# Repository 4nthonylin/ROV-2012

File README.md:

ROV-2012
========

Schematics, Code

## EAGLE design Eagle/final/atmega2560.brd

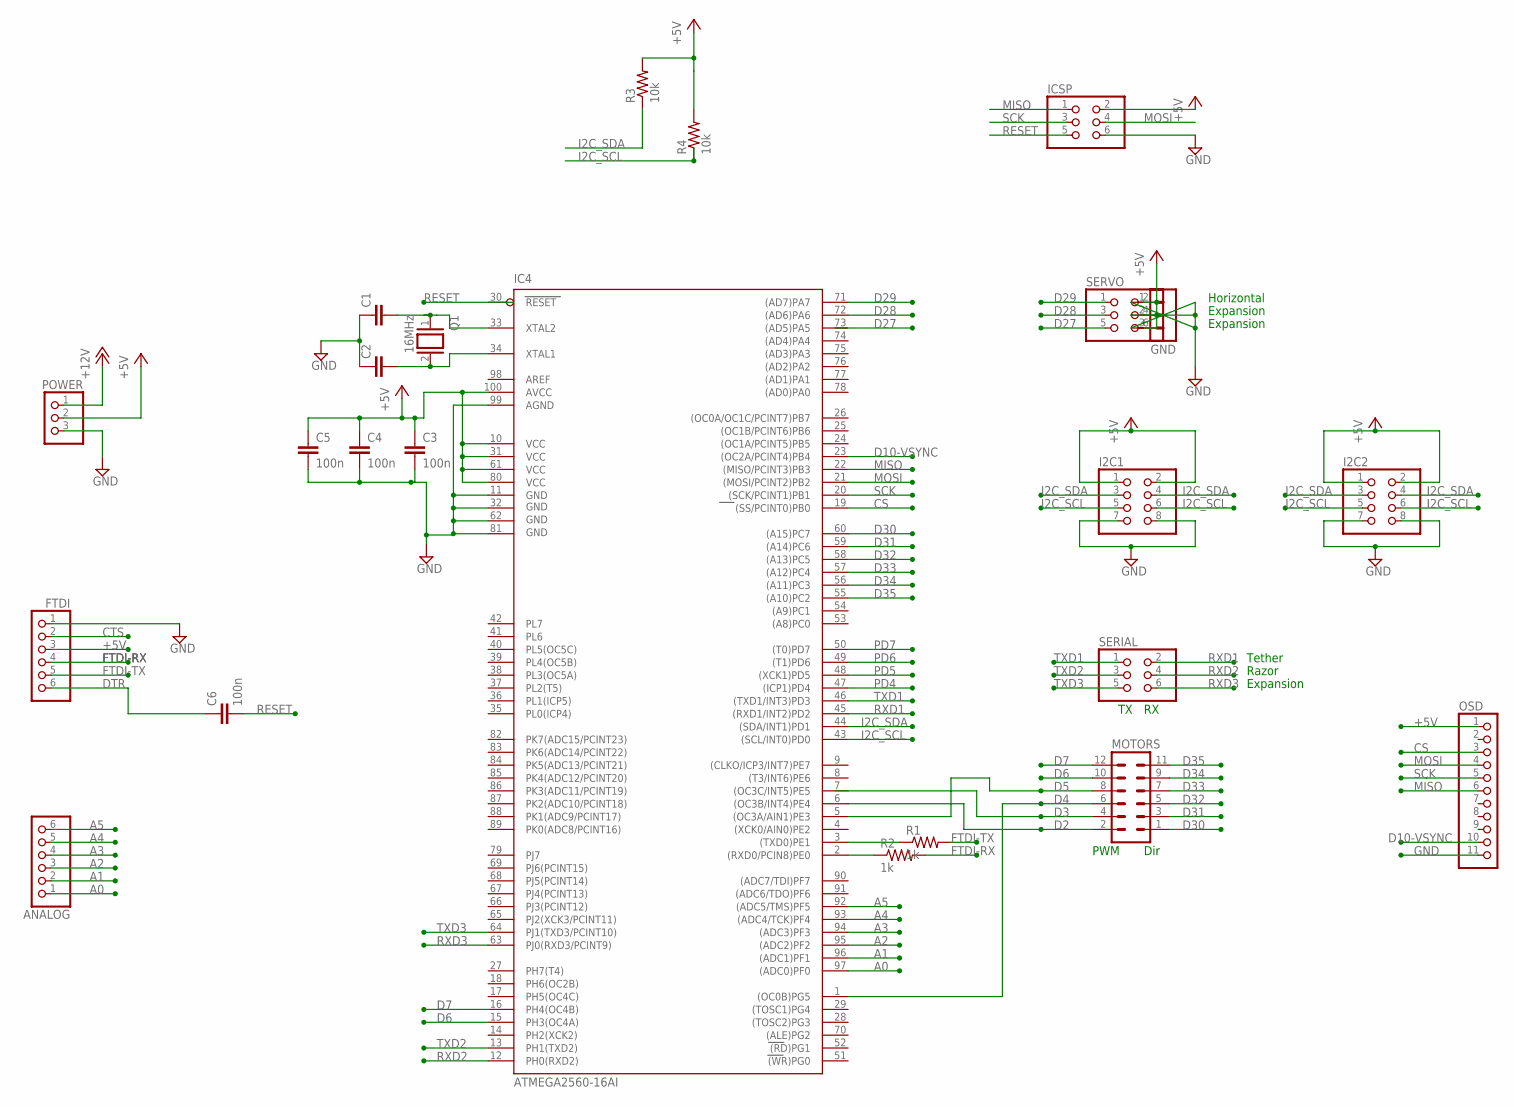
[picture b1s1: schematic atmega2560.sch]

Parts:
ANALOG: PINHD-1X6; 1X06
C1, C2: C5/3.5; C5B3.5
C3, C4, C5: 100n; C5B3.5
C6: 100n; C050-030X075
FTDI: PINHD-1X6; 1X06
GND: MA03-1
I2C1, I2C2: PINHD-2X4; 2X04
IC4: ATMEGA2560-16AI; TQFP100
ICSP: PINHD-2X3; 2X03
MOTORS: MA06-2
OSD: PINHD-1X11; 1X11
POWER: PINHD-1X3; 1X03
Q1: 16MHz; QS
R1, R2: 1k; 0207/7
R3, R4: 10k; 0207/7
SERIAL: PINHD-2X3; 2X03
SERVO: PINHD-2X3; 2X03

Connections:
+5V: C3.1, C4.1, C5.1, FTDI.3, I2C1.1, I2C1.2, I2C2.1, I2C2.2, IC4.10 (VCC), IC4.31 (VCC1), IC4.61 (VCC2), IC4.80 (VCC3), IC4.100 (AVCC), ICSP.2, OSD.1, POWER.2, R3.2, R4.2, SERVO.2, SERVO.4, SERVO.6
+12V: POWER.1
A0: ANALOG.1, IC4.97 ((ADC0)PF0)
A1: ANALOG.2, IC4.96 ((ADC1)PF1)
A2: ANALOG.3, IC4.95 ((ADC2)PF2)
A3: ANALOG.4, IC4.94 ((ADC3)PF3)
A4: ANALOG.5, IC4.93 ((ADC4/TCK)PF4)
A5: ANALOG.6, IC4.92 ((ADC5/TMS)PF5)
CS: IC4.19 ((SS/PCINT0)PB0), OSD.3
CTS: FTDI.2
D2: IC4.6 ((OC3B/INT4)PE4), MOTORS.2
D3: MOTORS.4
D4: IC4.1 ((OC0B)PG5), MOTORS.6
D5: IC4.5 ((OC3A/AIN1)PE3), MOTORS.8
D6: IC4.15 (PH3(OC4A)), MOTORS.10
D7: IC4.16 (PH4(OC4B)), MOTORS.12
D10-VSYNC: IC4.23 ((OC2A/PCINT4)PB4), OSD.10
D27: SERVO.5
D28: IC4.72 ((AD6)PA6), SERVO.3
D29: IC4.71 ((AD7)PA7), SERVO.1
D30: IC4.60 ((A15)PC7), MOTORS.1
D31: IC4.59 ((A14)PC6), MOTORS.3
D32: IC4.58 ((A13)PC5), MOTORS.5
D33: IC4.57 ((A12)PC4), MOTORS.7
D34: IC4.56 ((A11)PC3), MOTORS.9
D35: IC4.55 ((A10)PC2), MOTORS.11
DTR: C6.1, FTDI.6
FTDI-RX: FTDI.4, R2.2
FTDI-TX: FTDI.5, R1.2
GND: C1.1, C2.1, C3.2, C4.2, C5.2, FTDI.1, GND.1, GND.2, GND.3, I2C1.7, I2C1.8, I2C2.7, I2C2.8, IC4.11 (GND), IC4.32 (GND1), IC4.62 (GND2), IC4.81 (GND3), IC4.99 (AGND), ICSP.6, OSD.11, POWER.3
I2C_SCL: I2C1.5, I2C1.6, I2C2.5, I2C2.6, IC4.43 ((SCL/INT0)PD0), R4.1
I2C_SDA: I2C1.3, I2C1.4, I2C2.3, I2C2.4, IC4.44 ((SDA/INT1)PD1), R3.1
MISO: IC4.22 ((MISO/PCINT3)PB3), ICSP.1, OSD.6
MOSI: IC4.21 ((MOSI/PCINT2)PB2), ICSP.4, OSD.4
unnamed: C1.2, IC4.33 (XTAL2), Q1.1
unnamed: C2.2, IC4.34 (XTAL1), Q1.2
unnamed: IC4.2 ((RXD0/PCIN8)PE0), R2.1
unnamed: IC4.3 ((TXD0)PE1), R1.1
PD4: IC4.47 ((ICP1)PD4)
PD5: IC4.48 ((XCK1)PD5)
PD6: IC4.49 ((T1)PD6)
PD7: IC4.50 ((T0)PD7)
RESET: C6.2, ICSP.5
RXD1: IC4.45 ((RXD1/INT2)PD2), SERIAL.2
RXD2: IC4.12 (PH0(RXD2)), SERIAL.4
RXD3: IC4.63 (PJ0(RXD3/PCINT9)), SERIAL.6
SCK: IC4.20 ((SCK/PCINT1)PB1), ICSP.3, OSD.5
TXD1: IC4.46 ((TXD1/INT3)PD3), SERIAL.1
TXD2: IC4.13 (PH1(TXD2)), SERIAL.3
TXD3: IC4.64 (PJ1(TXD3/PCINT10)), SERIAL.5

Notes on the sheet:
PWM
Dir
Tether
Razor
Expansion
Horizontal

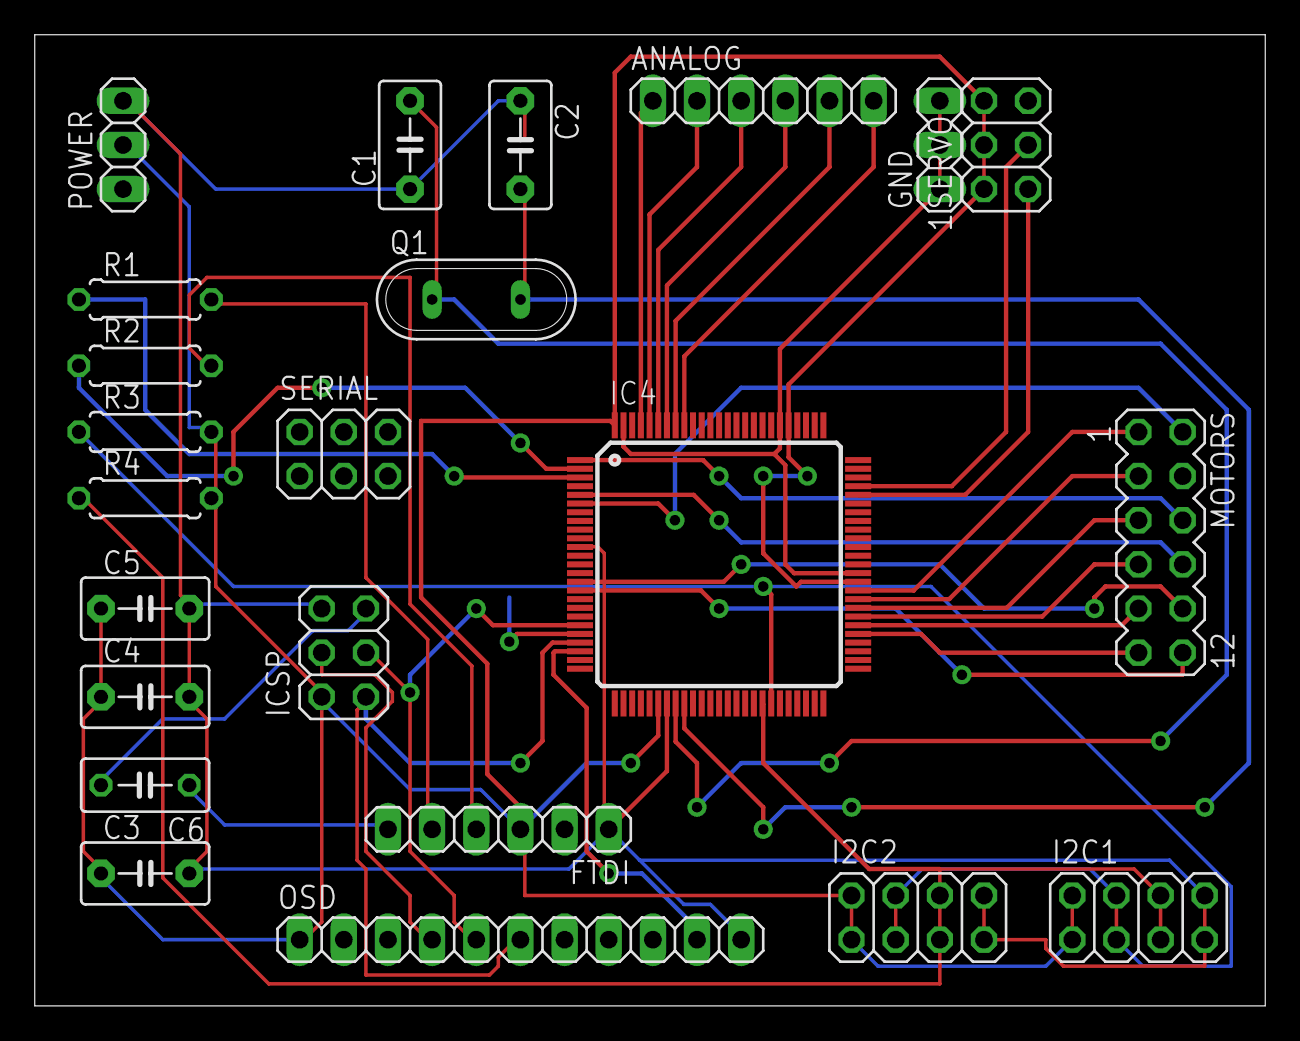
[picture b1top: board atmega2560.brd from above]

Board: 2 copper layers, 70.8 x 55.9 mm, 23 parts (0 on the bottom side), 42 nets.

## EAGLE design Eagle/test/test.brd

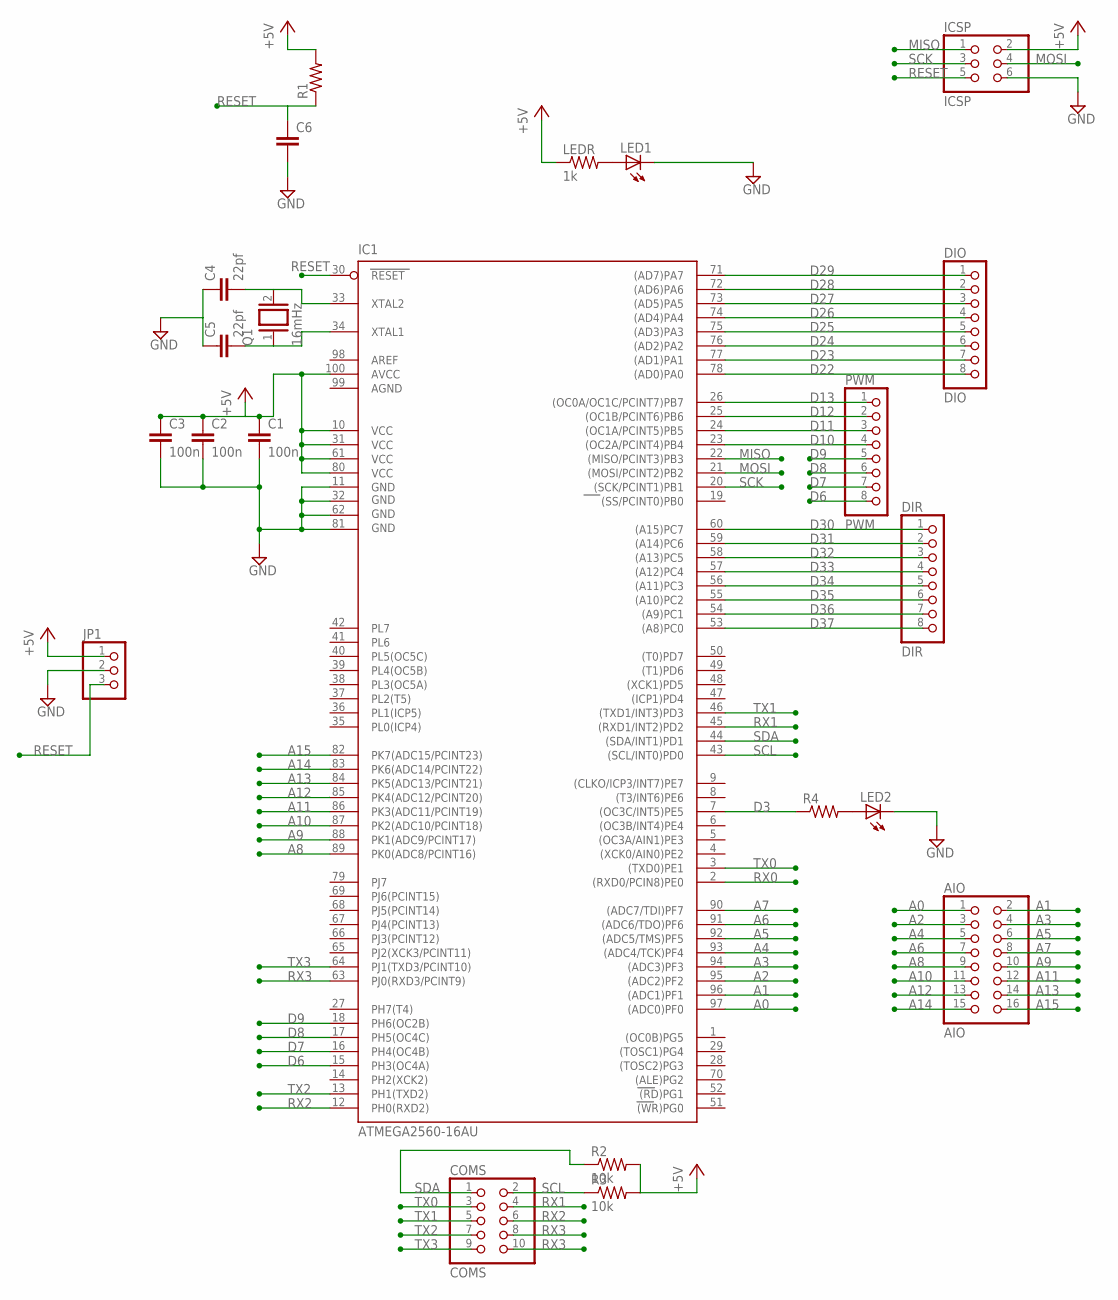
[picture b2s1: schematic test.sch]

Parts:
AIO: AIO; 2X08
C1, C2, C3: 100n; C5B3.5
C4, C5: 22pf; C5B3.5
C6: C5/3.5; C5B3.5
COMS: COMS; 2X05
DIO: DIO; 1X08
DIR: DIR; 1X08
IC1: ATMEGA2560-16AU; TQFP100
ICSP: ICSP; 2X03
JP1: PINHD-1X3; 1X03
LED1, LED2: LEDB156; Q62902-B156
LEDR: 1k; 0207/7
PWM: PWM; 1X08
Q1: 16mHz; QS
R1, R4: R-US_0207/7; 0207/7
R2, R3: 10k; 0207/7

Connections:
+5V: C1.1, C2.1, C3.1, IC1.10 (VCC), IC1.31 (VCC1), IC1.61 (VCC2), IC1.80 (VCC3), IC1.100 (AVCC), ICSP.2, JP1.1, LEDR.1, R1.2, R2.2, R3.2
A0: AIO.1, IC1.97 ((ADC0)PF0)
A1: AIO.2, IC1.96 ((ADC1)PF1)
A2: AIO.3, IC1.95 ((ADC2)PF2)
A3: AIO.4, IC1.94 ((ADC3)PF3)
A4: AIO.5, IC1.93 ((ADC4/TCK)PF4)
A5: AIO.6, IC1.92 ((ADC5/TMS)PF5)
A6: AIO.7, IC1.91 ((ADC6/TDO)PF6)
A7: AIO.8, IC1.90 ((ADC7/TDI)PF7)
A8: AIO.9, IC1.89 (PK0(ADC8/PCINT16))
A9: AIO.10, IC1.88 (PK1(ADC9/PCINT17))
A10: AIO.11, IC1.87 (PK2(ADC10/PCINT18))
A11: AIO.12, IC1.86 (PK3(ADC11/PCINT19))
A12: AIO.13, IC1.85 (PK4(ADC12/PCINT20))
A13: AIO.14, IC1.84 (PK5(ADC13/PCINT21))
A14: AIO.15, IC1.83 (PK6(ADC14/PCINT22))
A15: AIO.16, IC1.82 (PK7(ADC15/PCINT23))
AGND: IC1.99 (AGND)
D3: IC1.7 ((OC3C/INT5)PE5), R4.1
D6: IC1.15 (PH3(OC4A)), PWM.8
D7: IC1.16 (PH4(OC4B)), PWM.7
D8: IC1.17 (PH5(OC4C)), PWM.6
D9: IC1.18 (PH6(OC2B)), PWM.5
D10: IC1.23 ((OC2A/PCINT4)PB4), PWM.4
D11: IC1.24 ((OC1A/PCINT5)PB5), PWM.3
D12: IC1.25 ((OC1B/PCINT6)PB6), PWM.2
D13: IC1.26 ((OC0A/OC1C/PCINT7)PB7), PWM.1
D22: DIO.8, IC1.78 ((AD0)PA0)
D23: DIO.7, IC1.77 ((AD1)PA1)
D24: DIO.6, IC1.76 ((AD2)PA2)
D25: DIO.5, IC1.75 ((AD3)PA3)
D26: DIO.4, IC1.74 ((AD4)PA4)
D27: DIO.3, IC1.73 ((AD5)PA5)
D28: DIO.2, IC1.72 ((AD6)PA6)
D29: DIO.1, IC1.71 ((AD7)PA7)
D30: DIR.1, IC1.60 ((A15)PC7)
D31: DIR.2, IC1.59 ((A14)PC6)
D32: DIR.3, IC1.58 ((A13)PC5)
D33: DIR.4, IC1.57 ((A12)PC4)
D34: DIR.5, IC1.56 ((A11)PC3)
D35: DIR.6, IC1.55 ((A10)PC2)
D36: DIR.7, IC1.54 ((A9)PC1)
D37: DIR.8, IC1.53 ((A8)PC0)
GND: C1.2, C2.2, C3.2, C4.1, C5.1, C6.2, IC1.11 (GND), IC1.32 (GND1), IC1.62 (GND2), IC1.81 (GND3), ICSP.6, JP1.2, LED1.K (C), LED2.K (C)
MISO: IC1.22 ((MISO/PCINT3)PB3), ICSP.1
MOSI: IC1.21 ((MOSI/PCINT2)PB2), ICSP.4
unnamed: C4.2, IC1.33 (XTAL2), Q1.2
unnamed: C5.2, IC1.34 (XTAL1), Q1.1
unnamed: LED1.A, LEDR.2
unnamed: LED2.A, R4.2
RESET: C6.1, IC1.30 (RESET), ICSP.5, JP1.3, R1.1
RX0: IC1.2 ((RXD0/PCIN8)PE0)
RX1: COMS.4, IC1.45 ((RXD1/INT2)PD2)
RX2: COMS.6, IC1.12 (PH0(RXD2))
RX3: COMS.8, COMS.10, IC1.63 (PJ0(RXD3/PCINT9))
SCK: IC1.20 ((SCK/PCINT1)PB1), ICSP.3
SCL: COMS.2, IC1.43 ((SCL/INT0)PD0), R3.1
SDA: COMS.1, IC1.44 ((SDA/INT1)PD1), R2.1
TX0: COMS.3, IC1.3 ((TXD0)PE1)
TX1: COMS.5, IC1.46 ((TXD1/INT3)PD3)
TX2: COMS.7, IC1.13 (PH1(TXD2))
TX3: COMS.9, IC1.64 (PJ1(TXD3/PCINT10))

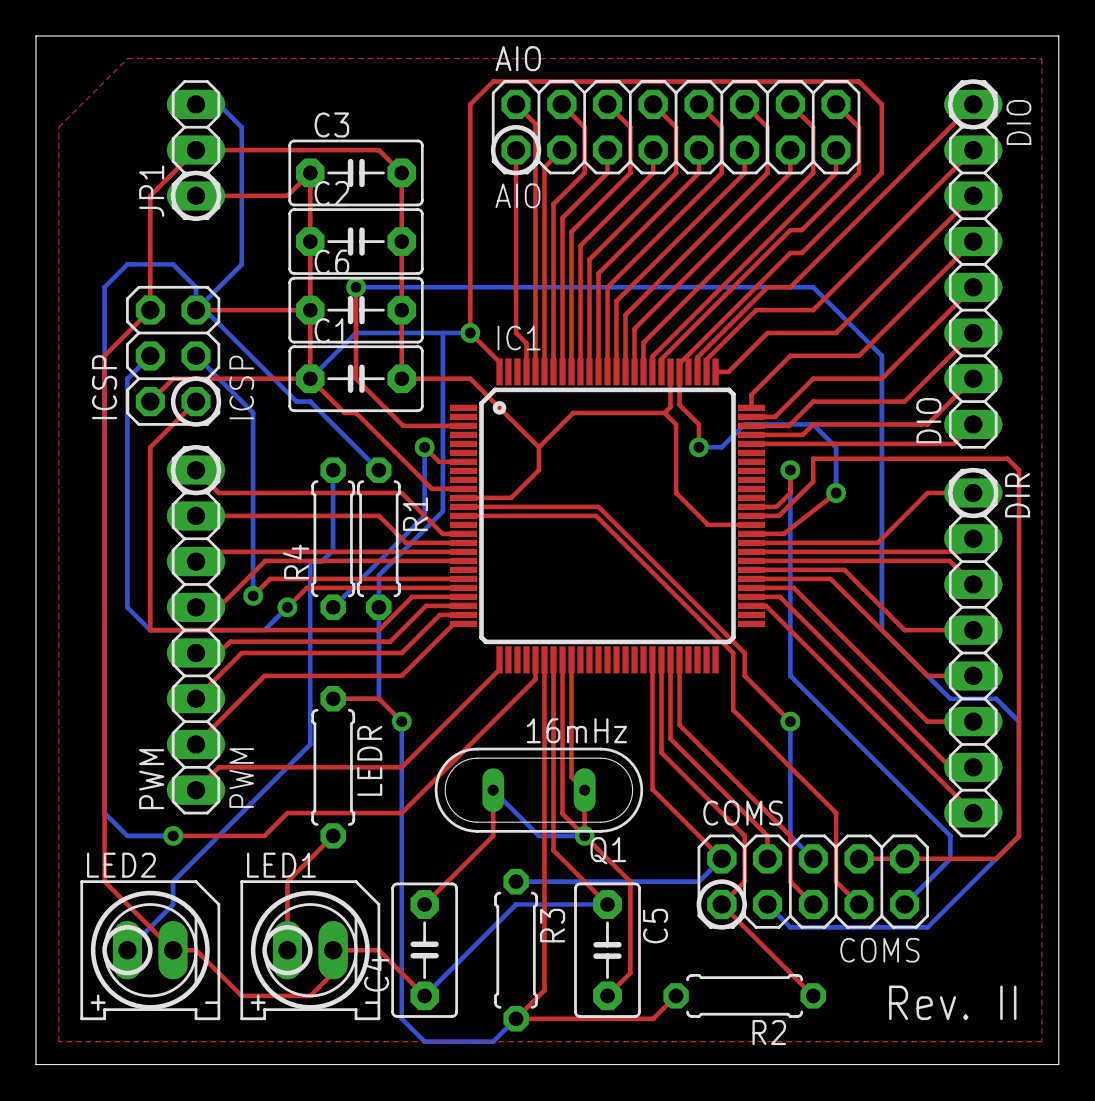
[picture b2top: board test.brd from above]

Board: 2 copper layers, 56.8 x 57.1 mm, 22 parts (0 on the bottom side), 60 nets.

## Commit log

2013-03-31 adding files
